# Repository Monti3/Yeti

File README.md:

# Yeti
> Yeti es un Robot creado en el marco de los Juegos Bonaerenses de Robotica. Capaz de competir en las disciplinas de Sumo, Velocidad y Control y Despejar el Area.

## Modo Sumo

Se trata de un modo en el cual se coloca a dos robots en una pista circular(dohyo) en forma de oposicion. Estos se deben empujar, y el primero en caerse perdera. Gana el mejor de tres rondas. Cabe destacar que este es un modo controlado, distinto de los demas que son totalmente autonomos.

## Modo Velocidad y Control

Consiste de un seguidor de linea: Se posiciona el robot en una pista blanca delimitada con negro y tiene que completar ese circuito en el menor tiempo posible.

## Modo despejar el Área

Se coloca el robot en un area blanca cuadrada con limites negros en la cual hay ciertos obstaculos. El robot debe limpiar este área en el menor tiempo posible. Si llegase a salir de la pista seraá penalizado.  

## Integrantes

* Juan Ignacio Montilla 
* Octavio Lautaro Pino 
* Tiago Luca Quattrocchi
* Joaquin Vignetta
* Santiago Alberto Zacarias

## 

[Página Web del proyecto](https://elyeti123.000webhostapp.com/)

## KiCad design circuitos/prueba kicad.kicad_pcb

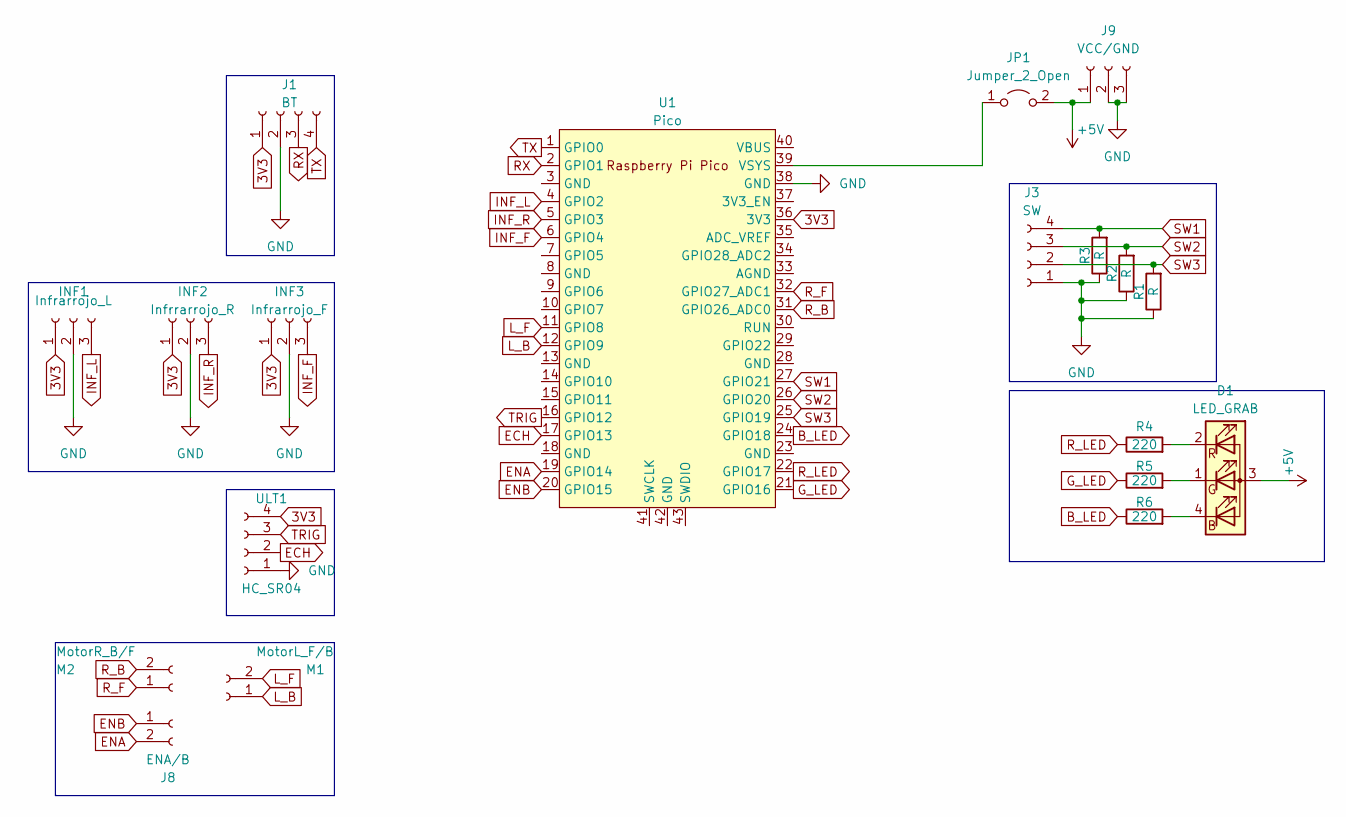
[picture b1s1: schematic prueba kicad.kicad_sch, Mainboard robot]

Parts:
D1: LED_GRAB; LED_D5.0mm-4_RGB_Wide_Pins
INF1: Infrarrojo_L; PinSocket_1x03_P2.54mm_Vertical
INF2: Infrrarrojo_R; PinSocket_1x03_P2.54mm_Vertical
INF3: Infrarrojo_F; PinSocket_1x03_P2.54mm_Vertical
J1: BT; PinSocket_1x04_P2.54mm_Vertical
J3: SW; PinSocket_1x04_P2.54mm_Vertical
J8: ENA/B; PinHeader_1x02_P2.54mm_Vertical
J9: VCC/GND; PinSocket_1x03_P2.54mm_Vertical
JP1: Jumper_2_Open; PinHeader_1x02_P2.54mm_Vertical
M1: MotorL_F/B; PinHeader_1x02_P2.54mm_Vertical
M2: MotorR_B/F; PinHeader_1x02_P2.54mm_Vertical
R1, R2, R3: R; R_Axial_DIN0207_L6.3mm_D2.5mm_P10.16mm_Horizontal
R4, R5, R6: 220; R_Axial_DIN0207_L6.3mm_D2.5mm_P10.16mm_Horizontal
U1: Pico; RPi_Pico_SMD_TH
ULT1: HC_SR04; PinSocket_1x04_P2.54mm_Vertical

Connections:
3V3: INF1.1, INF2.1, INF3.1, J1.1, U1.36 (3V3), ULT1.4
+5V: D1.3 (A), J9.1, JP1.2 (B)
B_LED: R6.1, U1.24 (GPIO18)
ECH: U1.17 (GPIO13), ULT1.2
ENA: J8.2, U1.19 (GPIO14)
ENB: J8.1, U1.20 (GPIO15)
GND: INF1.2, INF2.2, INF3.2, J1.2, J3.1, J9.2, J9.3, R1.1, R2.1, R3.1, U1.38 (GND), ULT1.1
G_LED: R5.1, U1.21 (GPIO16)
INF_F: INF3.3, U1.6 (GPIO4)
INF_L: INF1.3, U1.4 (GPIO2)
INF_R: INF2.3, U1.5 (GPIO3)
L_B: M1.1, U1.12 (GPIO9)
L_F: M1.2, U1.11 (GPIO8)
unnamed: D1.4 (BK), R6.2
unnamed: D1.1 (GK), R5.2
unnamed: D1.2 (RK), R4.2
unnamed: JP1.1 (A), U1.39 (VSYS)
RX: J1.3, U1.2 (GPIO1)
R_B: M2.2, U1.31 (GPIO26_ADC0)
R_F: M2.1, U1.32 (GPIO27_ADC1)
R_LED: R4.1, U1.22 (GPIO17)
SW1: J3.4, R3.2, U1.27 (GPIO21)
SW2: J3.3, R2.2, U1.26 (GPIO20)
SW3: J3.2, R1.2, U1.25 (GPIO19)
TRIG: U1.16 (GPIO12), ULT1.3
TX: J1.4, U1.1 (GPIO0)

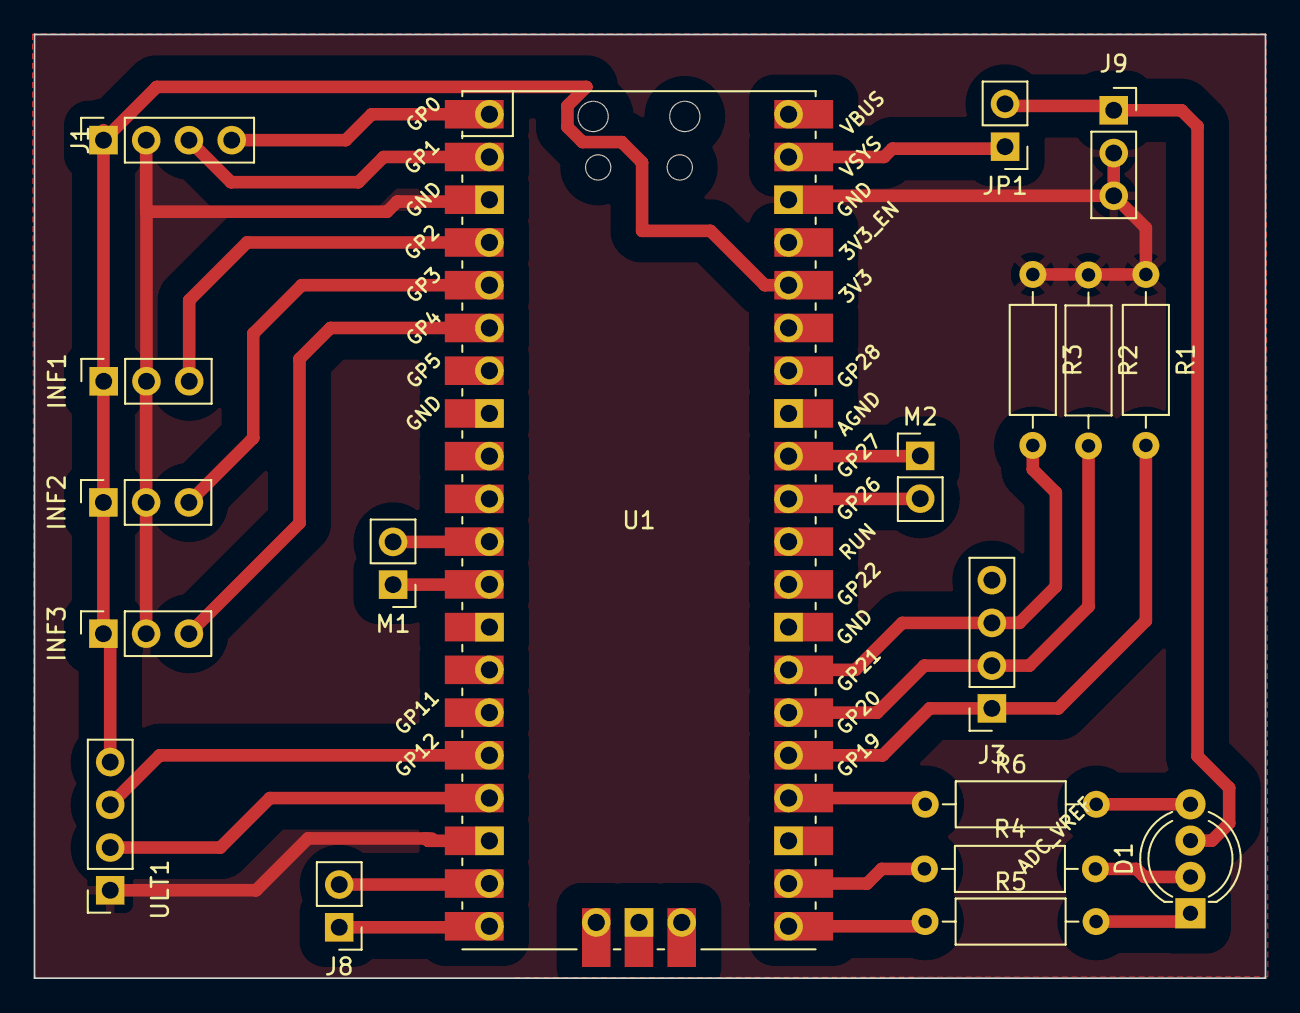
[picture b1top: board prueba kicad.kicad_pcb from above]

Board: 2 copper layers, 73.2 x 56.1 mm, 19 parts (0 on the bottom side), 26 nets.

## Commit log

2023-11-28 subo archivos de kicad
2023-11-28 subo docs
2023-11-28 subo datasheet de pico
2023-11-28 subo codigo
